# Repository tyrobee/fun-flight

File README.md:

# fun-flight
Fun Flight – Custom Flight Controller which is a STM37F722 based Fc which is leaned more towards planes and can be used for the drone too with a pwm escs.

the whole motivation behind building was that i was really motivated in making planes but all the plane flight controllers are really expensive for my hobby use case and while when it comes to fun flight its hobby grade great for anyone who doesnt want all the complicated gps and stuff in their plane and this can coustomized as they like as its completely open soucred by me ;)

## Key Features
	
- STM32F722 (ARM Cortex-M7, high-performance MCU)
- Designed primarily for RC planes
- Compatible with PWM ESCs (drone support)
- LQFP-64 package (compact and powerful)

## Schematics

## PCB 

## BOM

| Name                                      | Purpose   | Quantity | Total Cost (USD) | Link                                                                 | Distributor |
|-------------------------------------------|----------|----------|------------------|----------------------------------------------------------------------|-------------|
| XY301VA-5.0 XINYA 2 Pin Screw Terminal Block (Blue) | Connector | 10       | 1.27             | https://robu.in/product/xy301va-5-0-xinya-2-pin-screw-terminal-blockblue | Robu        |
| Male Pin Headers                          | Pins      | 5        | 0.79             | https://robu.in/product/ds1021-1x40sf11-b-connfly-1x40-pin-2-54mm-pin-header-v-t-type | Robu        |
| PCB with PCBA                             | PCB       | 1        | 177.00           | —                                                                    | JLCPCB      |

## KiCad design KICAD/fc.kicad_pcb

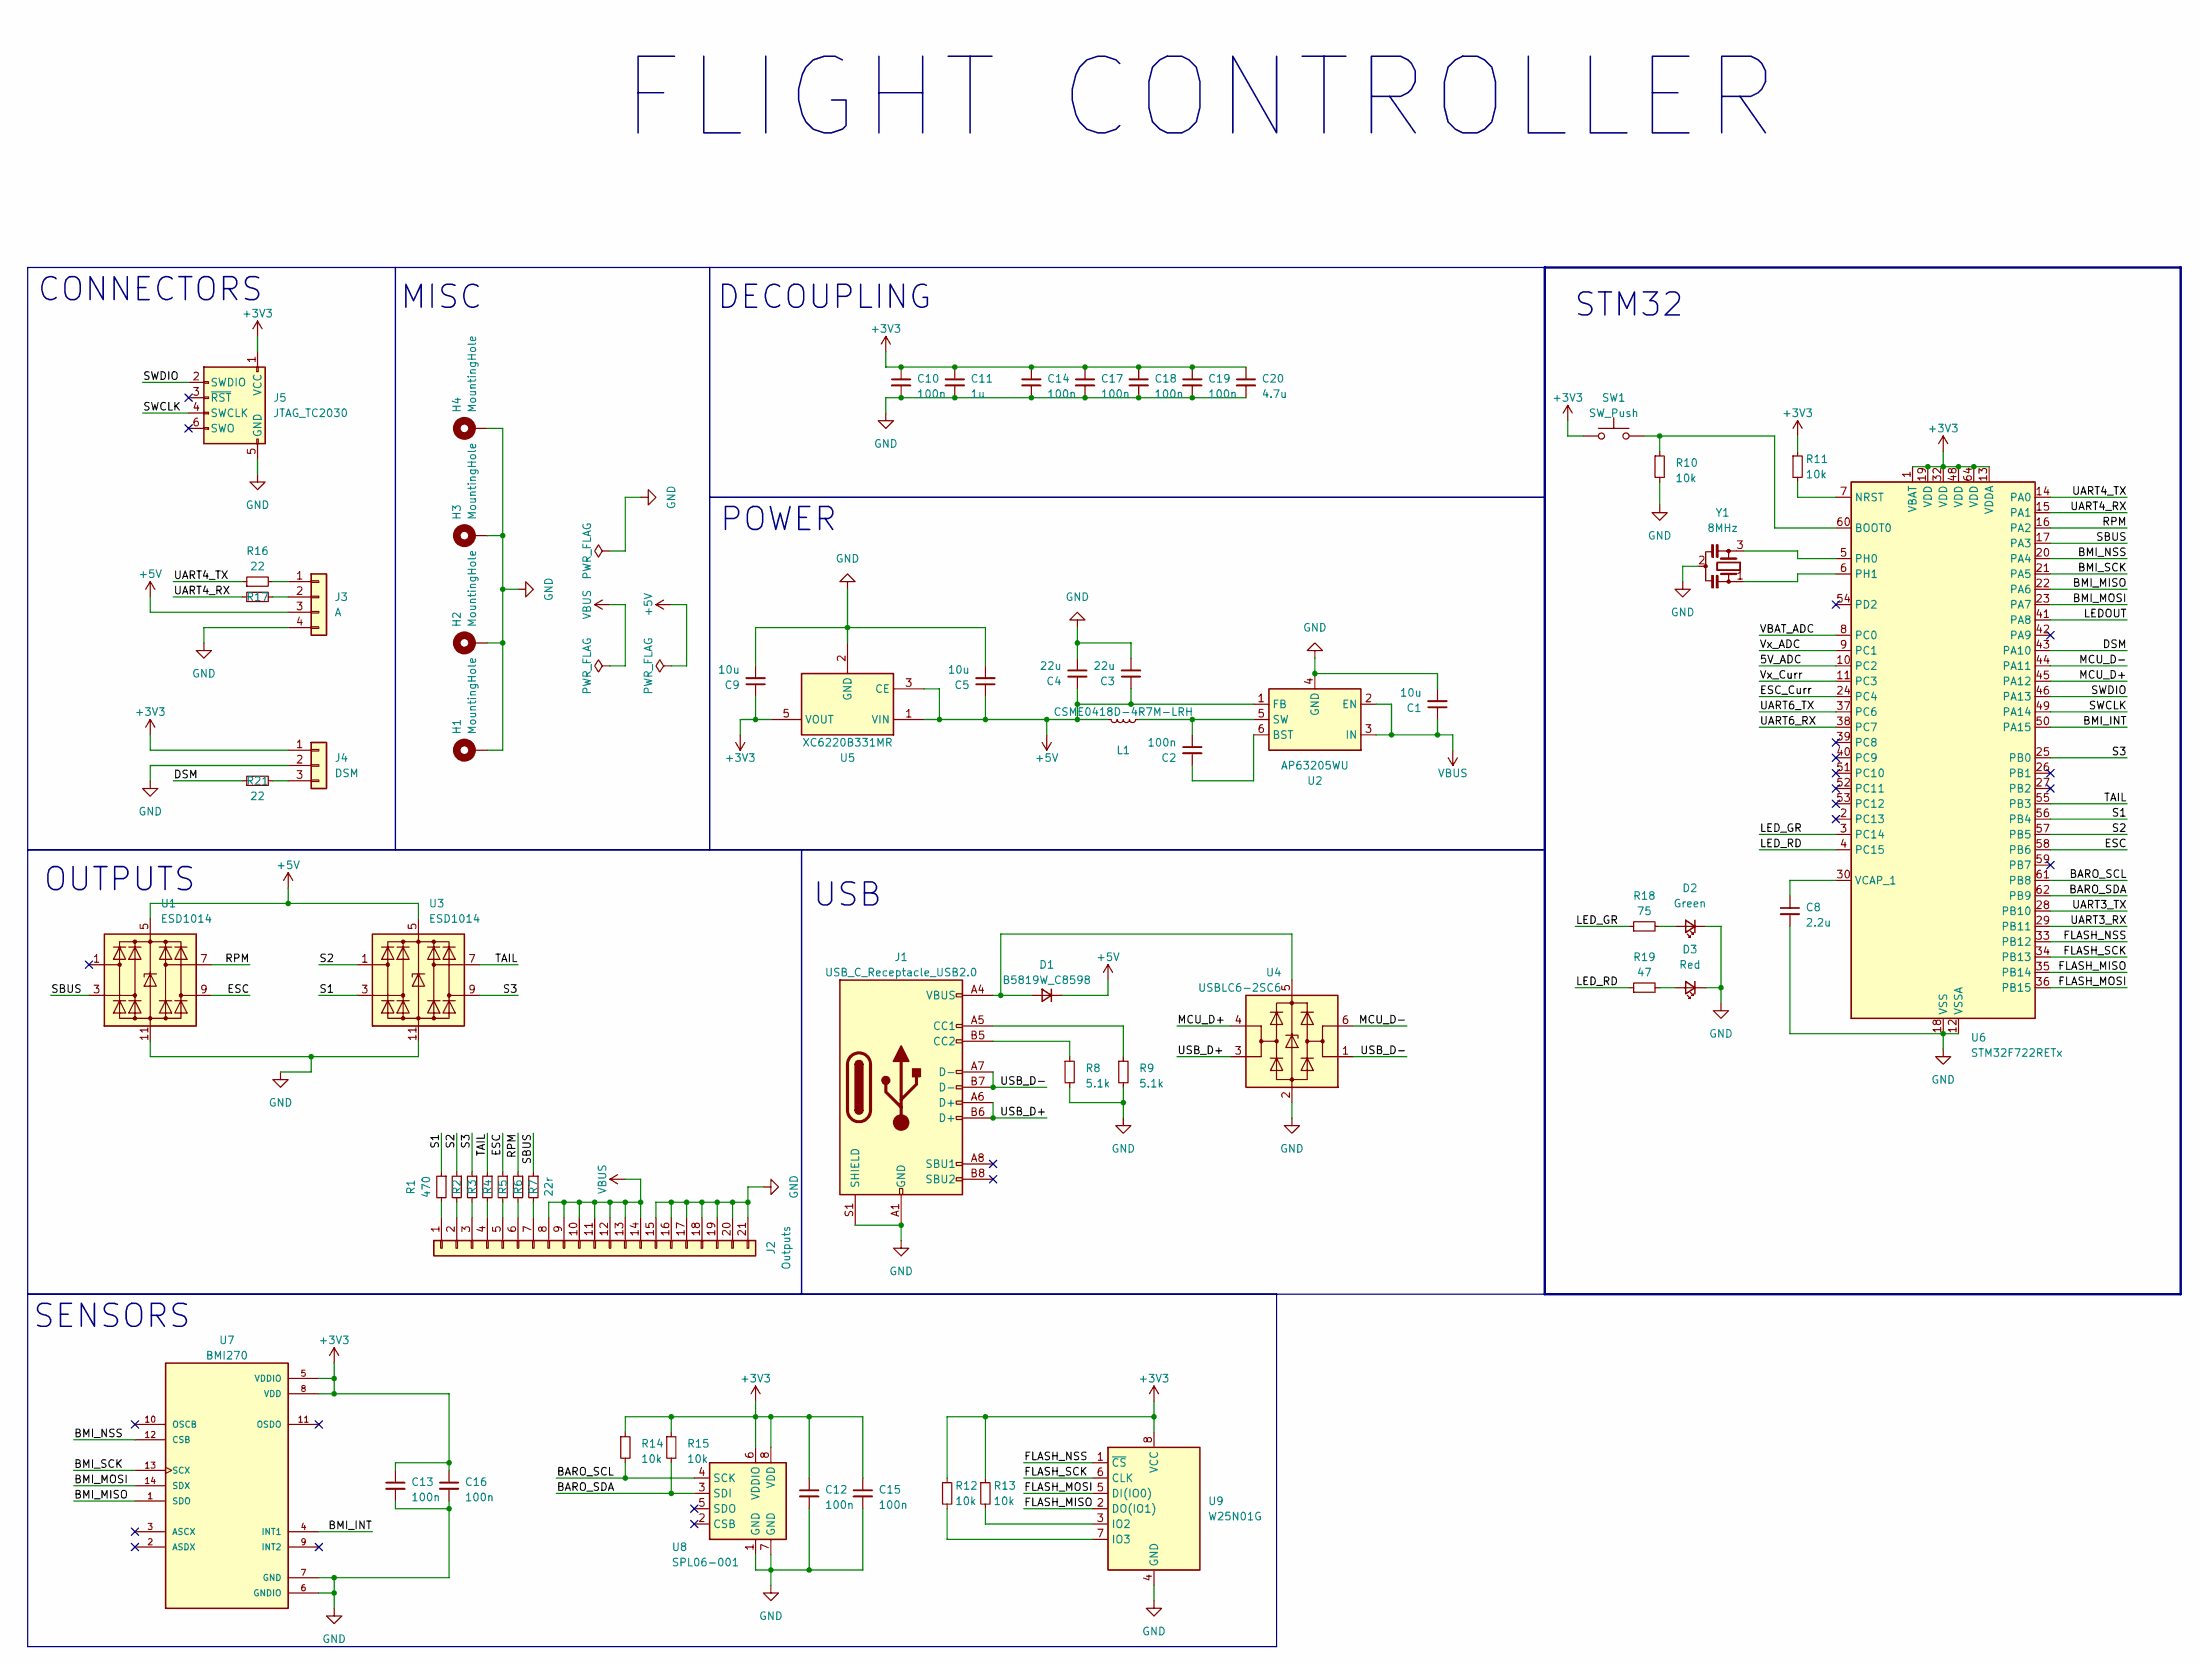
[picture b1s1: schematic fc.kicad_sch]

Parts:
C1, C5, C9: 10u; C_0603_1608Metric
C2, C10, C12, C13, C14, C15, C16, C17, C18, C19: 100n; C_0402_1005Metric
C3, C4: 22u; C_0603_1608Metric
C8: 2.2u; C_0402_1005Metric
C11: 1u; C_0402_1005Metric
C20: 4.7u; C_0402_1005Metric
D1: B5819W_C8598; D_SOD-123
D2: Green; LED_0603_1608Metric
D3: Red; LED_0603_1608Metric
H1, H2, H3, H4: MountingHole; MountingHole_2.2mm_M2_Pad_Via
J1: USB_C_Receptacle_USB2.0; USB_C_Receptacle_HRO_TYPE-C-31-M-12
J2: Outputs; 7xServo_Vertical
J3: A; JST_GH_BM04B-GHS-TBT_1x04-1MP_P1.25mm_Vertical
J4: DSM; JST_ZH_B3B-ZR_1x03_P1.50mm_Vertical
J5: JTAG_TC2030; CON_TC2030_outlined
L1: CSME0418D-4R7M-LRH; L_Vishay_IFSC-1515AH_4x4x1.8mm
R1, R2, R3, R4, R5, R6: 470; R_0402_1005Metric
R7: 22r; R_0402_1005Metric
R8, R9: 5.1k; R_0402_1005Metric
R10, R11, R12, R13, R14, R15: 10k; R_0402_1005Metric
R16, R17, R21: 22; R_0402_1005Metric
R18: 75; R_0402_1005Metric
R19: 47; R_0402_1005Metric
SW1: SW_Push; SW_Push_SPST_NO_Alps_SKRK
U1, U3: ESD1014; DFN-10-1EP_2.6x2.6mm_P0.5mm_EP1.3x2.2mm
U2: AP63205WU; TSOT-23-6
U4: USBLC6-2SC6; SOT-23-6
U5: XC6220B331MR; SOT-23-5
U6: STM32F722RETx; LQFP-64_10x10mm_P0.5mm
U7: BMI270; XDCR_BMI270
U8: SPL06-001; Bosch_LGA-8_2x2.5mm_P0.65mm_ClockwisePinNumbering
U9: W25N01G; WSON-8-1EP_8x6mm_P1.27mm_EP3.4x4.3mm
Y1: 8MHz; Resonator_SMD_Murata_CSTxExxV-3Pin_3.0x1.1mm

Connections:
+3V3: C9.1, C10.1, C11.1, C12.1, C13.1, C14.1, C15.1, C16.1, C17.1, C18.1, C19.1, C20.1, J4.1, J5.1 (VCC), R11.1, R12.1, R13.1, R14.1, R15.1, SW1.1, U5.5 (VOUT), U6.1 (VBAT), U6.13 (VDDA), U6.19 (VDD), U6.32 (VDD), U6.48 (VDD), U6.64 (VDD), U7.5 (VDDIO), U7.8 (VDD), U8.6 (VDDIO), U8.8 (VDD), U9.8 (VCC)
+5V: C3.1, C4.1, C5.1, D1.1 (K), J3.3, L1.2, U1.5 (VBUS), U2.1 (FB), U3.5 (VBUS), U5.1 (VIN), U5.3 (CE)
/5V_ADC: U6.10 (PC2)
/BARO_SCL: R14.2, U6.61 (PB8), U8.4 (SCK)
/BARO_SDA: R15.2, U6.62 (PB9), U8.3 (SDI)
/BMI_INT: U6.50 (PA15), U7.4 (INT1)
/BMI_MISO: U6.22 (PA6), U7.1 (SDO)
/BMI_MOSI: U6.23 (PA7), U7.14 (SDX)
/BMI_NSS: U6.20 (PA4), U7.12 (CSB)
/BMI_SCK: U6.21 (PA5), U7.13 (SCX)
/DSM: R21.1, U6.43 (PA10)
/ESC: R5.1, U1.9 (I/O4), U6.58 (PB6)
/ESC_Curr: U6.24 (PC4)
/FLASH_MISO: U6.35 (PB14), U9.2 (DO(IO1))
/FLASH_MOSI: U6.36 (PB15), U9.5 (DI(IO0))
/FLASH_NSS: U6.33 (PB12), U9.1 (~CS)
/FLASH_SCK: U6.34 (PB13), U9.6 (CLK)
/LEDOUT: U6.41 (PA8)
/LED_GR: R18.1, U6.3 (PC14)
/LED_RD: R19.1, U6.4 (PC15)
/MCU_D+: U4.4 (I/O2), U6.45 (PA12)
/MCU_D-: U4.6 (I/O1), U6.44 (PA11)
/RPM: R6.1, U1.7 (I/O3), U6.16 (PA2)
/S1: R1.1, U3.3 (I/O2), U6.56 (PB4)
/S2: R2.1, U3.1 (I/O1), U6.57 (PB5)
/S3: R3.1, U3.9 (I/O4), U6.25 (PB0)
/SBUS: R7.1, U1.3 (I/O2), U6.17 (PA3)
/SWCLK: J5.4 (SWCLK), U6.49 (PA14)
/SWDIO: J5.2 (SWDIO), U6.46 (PA13)
/TAIL: R4.1, U3.7 (I/O3), U6.55 (PB3)
/UART3_RX: U6.29 (PB11)
/UART3_TX: U6.28 (PB10)
/UART4_RX: R17.1, U6.15 (PA1)
/UART4_TX: R16.1, U6.14 (PA0)
/UART6_RX: U6.38 (PC7)
/UART6_TX: U6.37 (PC6)
/USB_D+: J1.A6 (D+), J1.B6 (D+), U4.3 (I/O2)
/USB_D-: J1.A7 (D-), J1.B7 (D-), U4.1 (I/O1)
/VBAT_ADC: U6.8 (PC0)
/Vx_ADC: U6.9 (PC1)
/Vx_Curr: U6.11 (PC3)
GND: C1.2, C3.2, C4.2, C5.2, C8.2, C9.2, C10.2, C11.2, C12.2, C13.2, C14.2, C15.2, C16.2, C17.2, C18.2, C19.2, C20.2, D2.1 (K), D3.1 (K), H1.1, H2.1, H3.1, H4.1, J1.A1 (GND), J1.A12 (GND), J1.B1 (GND), J1.B12 (GND), J1.S1 (SHIELD), J2.15, J2.16, J2.17, J2.18, J2.19, J2.20, J2.21, J3.4, J4.2, J5.5 (GND), R8.2, R9.2, R10.2, U1.11 (GND), U2.4 (GND), U3.11 (GND), U4.2 (GND), U5.2 (GND), U6.12 (VSSA), U6.18 (VSS), U6.31 (VSS), U6.47 (VSS), U6.63 (VSS), U7.6 (GNDIO), U7.7 (GND), U8.1 (GND), U8.7 (GND), U9.4 (GND), Y1.2
unnamed: D1.2 (A), J1.A4 (VBUS), J1.A9 (VBUS), J1.B4 (VBUS), J1.B9 (VBUS), U4.5 (VBUS)
unnamed: D2.2 (A), R18.2
unnamed: D3.2 (A), R19.2
unnamed: J1.A5 (CC1), R9.1
unnamed: J1.B5 (CC2), R8.1
unnamed: J2.1, R1.2
unnamed: J2.2, R2.2
unnamed: J2.3, R3.2
unnamed: J2.4, R4.2
unnamed: J2.5, R5.2
unnamed: J2.6, R6.2
unnamed: J2.7, R7.2
unnamed: J3.1, R16.2
unnamed: J3.2, R17.2
unnamed: J4.3, R21.2
unnamed: C2.2, U2.6 (BST)
unnamed: C2.1, L1.1, U2.5 (SW)
unnamed: R10.1, SW1.2, U6.60 (BOOT0)
unnamed: R11.2, U6.7 (NRST)
unnamed: U6.5 (PH0), Y1.3
unnamed: U6.6 (PH1), Y1.1
unnamed: C8.1, U6.30 (VCAP_1)
unnamed: R13.2, U9.3 (IO2)
unnamed: R12.2, U9.7 (IO3)
VBUS: C1.1, J2.8, J2.9, J2.10, J2.11, J2.12, J2.13, J2.14, U2.2 (EN), U2.3 (IN)

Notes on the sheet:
USB
POWER
MISC
CONNECTORS
OUTPUTS
DECOUPLING
FLIGHT CONTROLLER
STM32
SENSORS

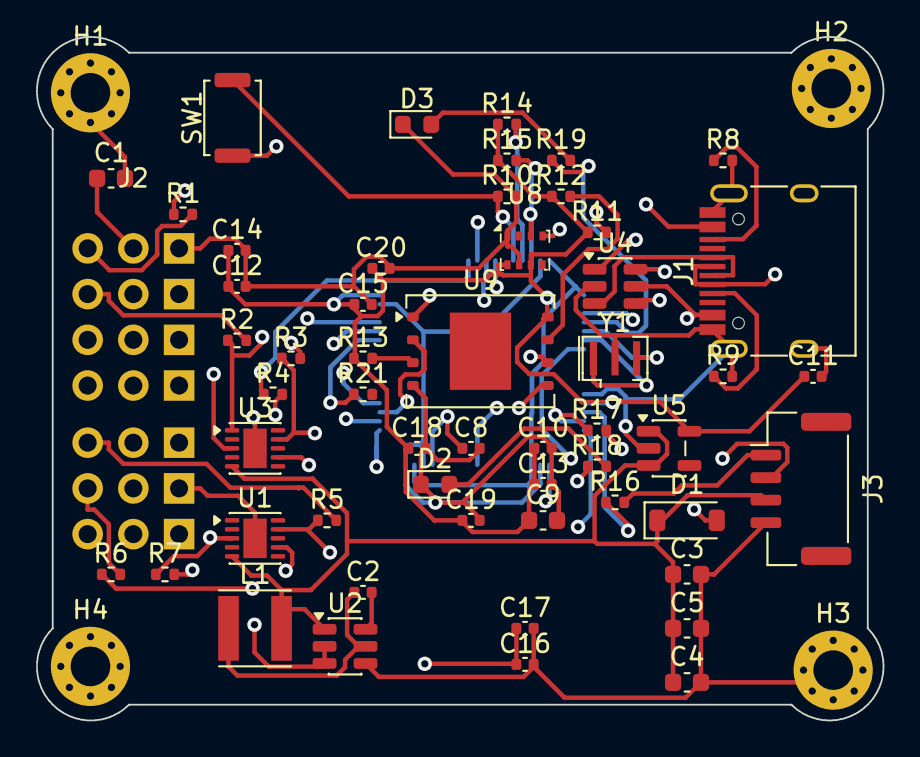
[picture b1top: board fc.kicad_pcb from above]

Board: 2 copper layers, 47.0 x 38.0 mm, 59 parts (1 on the bottom side), 49 nets.

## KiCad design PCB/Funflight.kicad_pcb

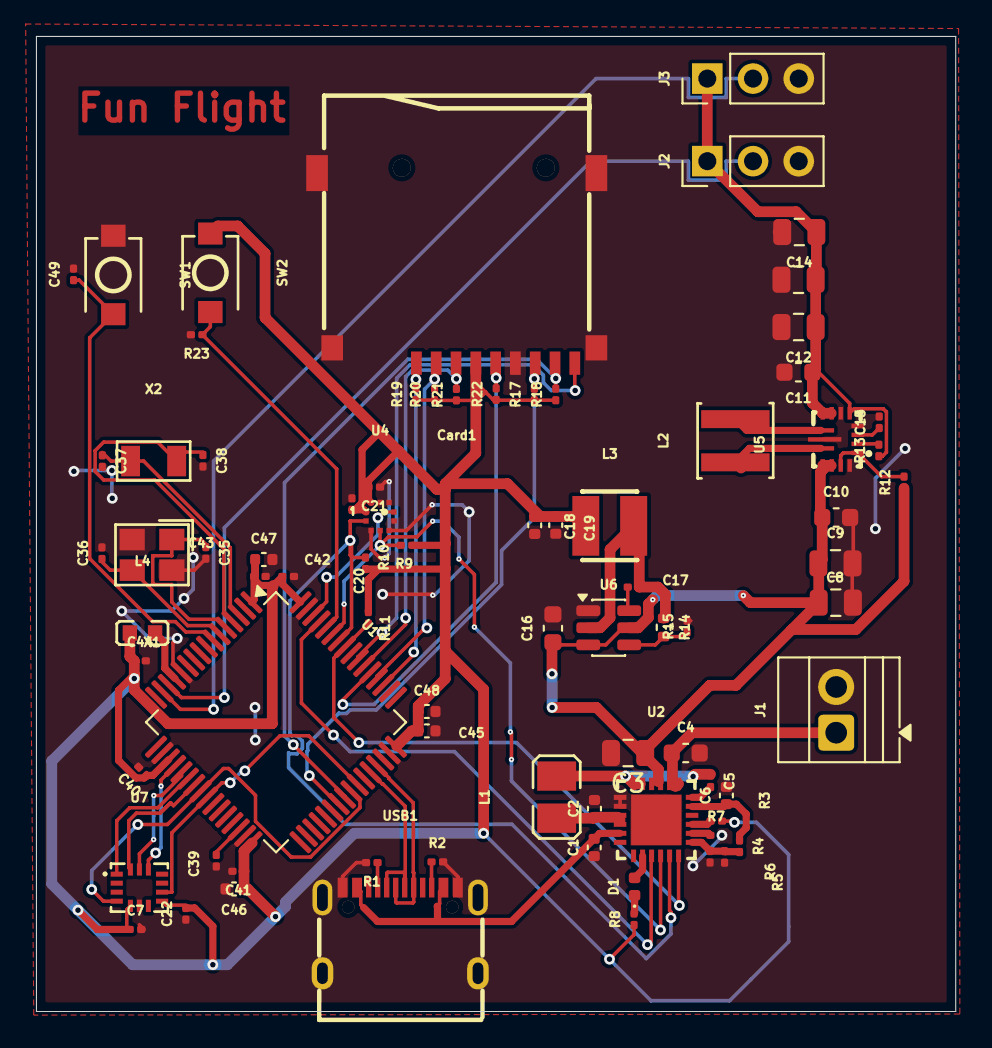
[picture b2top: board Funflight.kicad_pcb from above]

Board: 2 copper layers, 51.1 x 54.2 mm, 79 parts (0 on the bottom side), 55 nets.

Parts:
C1, C45, C46, C47: 1uF; C_0402_1005Metric
C2, C6, C48: 10uF; C_0402_1005Metric
C3: 44uF; C_0805_2012Metric
C4, C10, C11: 10uF; C_0603_1608Metric
C5: 47nF; C_0201_0603Metric
C7, C15, C17, C20, C21, C22, C40, C41, C42, C43, C44, C49: 100nF; C_0201_0603Metric
C8, C9: 10uF; C_0805_2012Metric
C12, C13, C14: 22uF; C_0805_2012Metric
C16: 2.2uF; C_0603_1608Metric
C18, C19: 22uF; C_0402_1005Metric
C35, C36: 20pF; C_0201_0603Metric
C37, C38: 6.8pF; C_0201_0603Metric
C39: 2.2uF; C_0201_0603Metric
Card1: TF-01A; TF-SMD_TF-01A
D1: LED; LED_0402_1005Metric
J1: Screw_Terminal_01x02; TerminalBlock_Xinya_XY308-2.54-2P_1x02_P2.54mm_Horizontal
J2, J3: Conn_01x03; PinHeader_1x03_P2.54mm_Vertical
L1: 1uH; L2520
L2: 1.5uH; IND-SMD_L4.0-W4.0-A
L3: 5.6uH; IND-SMD_L3.0-W3.0
L4: FCM1608KF-601T03; L0603
R1, R2: 5.1K; R_0201_0603Metric
R3, R6, R8, R9, R10, R11, R12, R13, R17, R18, R19, R20, R21, R22, R23: 10K; R_0201_0603Metric
R4: 5.23K; R_0201_0603Metric
R5: 30.1K; R_0201_0603Metric
R7: 383; R_0201_0603Metric
R14: 100K; R_0402_1005Metric
R15: 22.1K; R_0201_0603Metric
SW1, SW2: TS-1088-AR02016; SW-SMD_L3.9-W3.0-P4.45
U1: STM32F722RETx; LQFP-64_10x10mm_P0.5mm
U2: BQ25883RGER; VFQFPN-24_L4.0-W4.0-P0.50-BL-EP2.8
U4: BMP580; LGA-10_L2.0-W2.0-P0.50-TL_BMP580
U5: TPS63070RNMR; VQFN-HR-15_L3.0-W2.5-P0.50-BL_TPS63070RNMR
U6: LMR51430; SOT-23-6
U7: ICM-45686; LGA-14_L3.0-W2.5-P0.50-TL
USB1: TYPE-C 16PIN 2MD(073); USB-C-SMD_TYPE-C-6PIN-2MD-073
X1: X322525MOB4SI; CRYSTAL-SMD_4P-L3.2-W2.5-BL
X2: X321532768KGD2SI; OSC-SMD_L3.2-W1.5

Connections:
+3.3V: C7.1, C18.2, C19.2, C20.1, C21.2, C22.2, C40.1, C41.1, C42.1, C43.1, C44.1, C45.1, C46.1, C47.1, C48.1, Card1.4 (VDD), L3.2, L4.1, R3.1, R8.1, R9.1, R10.1, R11.1, R17.1, R18.1, R19.1, R20.1, R21.1, R22.1, SW2.1, U1.1 (VBAT), U1.19 (VDD), U1.32 (VDD), U1.48 (VDD), U1.64 (VDD), U4.1 (VDDIO), U4.10 (VDD), U7.5 (VDDIO), U7.8 (VDD)
+5V: C11.1, C12.1, C13.1, C14.1, J2.1, J3.1, R13.1, U5.5 (FB), U5.7 (Vout), U5.8 (Vout)
+BATT: C4.1, J1.1, U2.13 (BAT), U2.14 (BAT)
/BMP_INT: U1.62 (PB9), U4.7 (INT)
/BOOT: R23.1, SW2.2, U1.60 (BOOT0)
/BQ_CE: U1.61 (PB8), U2.3 (~CE)
/BQ_INT: R11.2, U1.57 (PB5), U2.6 (~INT)
/BQ_PG: R3.2, U2.9 (~PG)
/BTST: C5.1, L1.2, U2.17 (SW), U2.18 (SW)
/HSE_IN: C35.1, U1.5 (PH0), X1.1 (OSC1)
/HSE_OUT: C36.1, U1.6 (PH1), X1.3 (OSC2)
/I2C_SCL: R10.2, U1.58 (PB6), U2.5 (SCL), U4.2 (SCK)
/I2C_SDA: R9.2, U1.59 (PB7), U2.4 (SDA), U4.4 (SDI)
/ICM_CS: U1.20 (PA4), U7.12 (AP_CS)
/ICM_INT1: U1.24 (PC4), U1.41 (PA8), U7.4 (INT1/INT)
/ICM_INT2: U1.25 (PB0), U1.42 (PA9), U7.9 (INT2/FSYNC/CLKIN)
/ICM_SCK: U1.21 (PA5), U7.13 (AP_SCL/AP_SCLK)
/ICM_SDI: U1.23 (PA7), U7.14 (AP_SDA/AP_SDIO/AP_SDI)
/ICM_SDO: U1.22 (PA6), U7.1 (AP_SDO/AP_AD0)
/LSE_IN: C37.1, U1.3 (PC14), X2.1
/LSE_OUT: C38.1, U1.4 (PC15), X2.2
/RESET: C49.1, SW1.2, U1.7 (NRST)
/SD_CD: Card1.9 (CD), U1.55 (PB3)
/SD_CLK: Card1.5 (CLK(SCLK)), R22.2, U1.53 (PC12)
/SD_CMD: Card1.3 (CMD(DI)), R21.2, U1.54 (PD2)
/SD_DAT0: Card1.7 (DAT0(D0)), R17.2, U1.39 (PC8)
/SD_DAT1: Card1.8 (DAT1(RSV)), R18.2, U1.40 (PC9)
/SD_DAT2: Card1.1 (DAT2(RSV)), R19.2, U1.51 (PC10)
/SD_DAT3: Card1.2 (CDDAT3(CS)), R20.2, U1.52 (PC11)
/SERVO1: J2.2, U1.14 (PA0)
/SERVO2: J3.2, U1.15 (PA1)
/USB_DN: U1.44 (PA11), USB1.5 (DN2), USB1.7 (DN1)
/USB_DP: U1.45 (PA12), USB1.6 (DP1), USB1.8 (DP2)
GND: C1.1, C2.2, C3.2, C4.2, C6.2, C7.2, C8.2, C9.2, C10.2, C11.2, C12.2, C13.2, C14.2, C15.2, C16.2, C18.1, C19.1, C20.2, C21.1, C22.1, C35.2, C36.2, C37.2, C38.2, C39.2, C40.2, C41.2, C42.2, C43.2, C44.2, C45.2, C46.2, C47.2, C48.2, C49.2, Card1.6 (VSS), Card1.10 (GND), Card1.11 (GND), Card1.12 (GND), Card1.13 (GND), J1.2, J2.3, J3.3, R1.2, R2.2, R5.2, R6.2, R7.2, R15.2, R23.2, SW1.1, U1.12 (VSSA), U1.18 (VSS), U1.31 (VSS), U1.47 (VSS), U1.63 (VSS), U2.19 (GND), U2.20 (GND), U2.25 (EP), U4.3 (VSS), U4.5 (SDO), U4.6 (CSB), U4.8 (VSS), U4.9 (VSS), U5.4 (GND), U5.6 (FB2), U5.10 (PGND), U5.15 (Vsel), U6.1 (GND), U7.6 (GND), USB1.1 (GND), USB1.12 (GND), USB1.13 (SHELL), USB1.14 (SHELL), X1.2 (GND), X1.4 (GND)
unnamed: C2.1, L1.1, U2.21 (PMID), U2.22 (PMID)
unnamed: D1.2 (A), U2.2 (STAT)
unnamed: D1.1 (K), R8.2
unnamed: C39.1, U1.30 (VCAP_1)
unnamed: L4.2, U1.13 (VDDA)
unnamed: C5.2, U2.12 (BTST)
unnamed: R7.1, U2.8 (ILIM)
unnamed: R4.2, R5.1, R6.1, U2.7 (TS)
unnamed: R12.2, U5.1 (PS/SYNC), U5.14 (EN)
unnamed: L2.1, U5.11 (L1)
unnamed: L2.2, U5.9 (L2)
unnamed: R13.2, U5.2 (PG)
unnamed: C15.1, U5.3 (Vaux)
unnamed: C17.1, U6.6 (CB)
unnamed: R14.2, R15.1, U6.4 (FB)
unnamed: C17.2, L3.1, R14.1, U6.2 (SW)
unnamed: R1.1, USB1.4 (CC1)
unnamed: R2.1, USB1.10 (CC2)
VBUS: C1.2, U2.23 (VBUS), USB1.2 (VBUS), USB1.11 (VBUS)
VREGN: C6.1, R4.1, U2.11 (REGN)
VSYS: C3.1, C8.1, C9.1, C10.1, C16.1, R12.1, U2.15 (SYS), U2.16 (SYS), U5.12 (Vin), U5.13 (Vin), U6.3 (VIN), U6.5 (EN)

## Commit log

2025-12-31 gerber
2025-12-31 Update README with flight controller features and images
    Add detailed features and images of the flight controller.
2025-12-31 Fix image paths and descriptions in README
    Updated image references and descriptions in README.
2026-01-01 new_README
2026-01-01 Fix image paths for PCB renders in README
    Corrected image paths in PCB renders section.
2026-01-06 new readme
2026-03-23 Firmware addition
2026-03-23 Enhance README with motivation and feature details
    Added motivation section and improved feature list clarity.
2026-03-26 Update PCB images in README
2026-03-26 Revise key features in README.md
    Updated key features section with new components and specifications.
2026-03-27 Fix duplicate entries in Key Features section
    Removed duplicate key features from README.
2026-03-27 Update key features in README.md for clarity
2026-03-27 Update schematic image reference in README
2026-04-02 Add Step.zip
